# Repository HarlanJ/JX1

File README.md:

# JX1
The JX1 is an open source 3D printer in progress. It uses custom software on a Raspberry Pi and custom Arduino firmware. This project is created by John Harlan with help from Edward Green.

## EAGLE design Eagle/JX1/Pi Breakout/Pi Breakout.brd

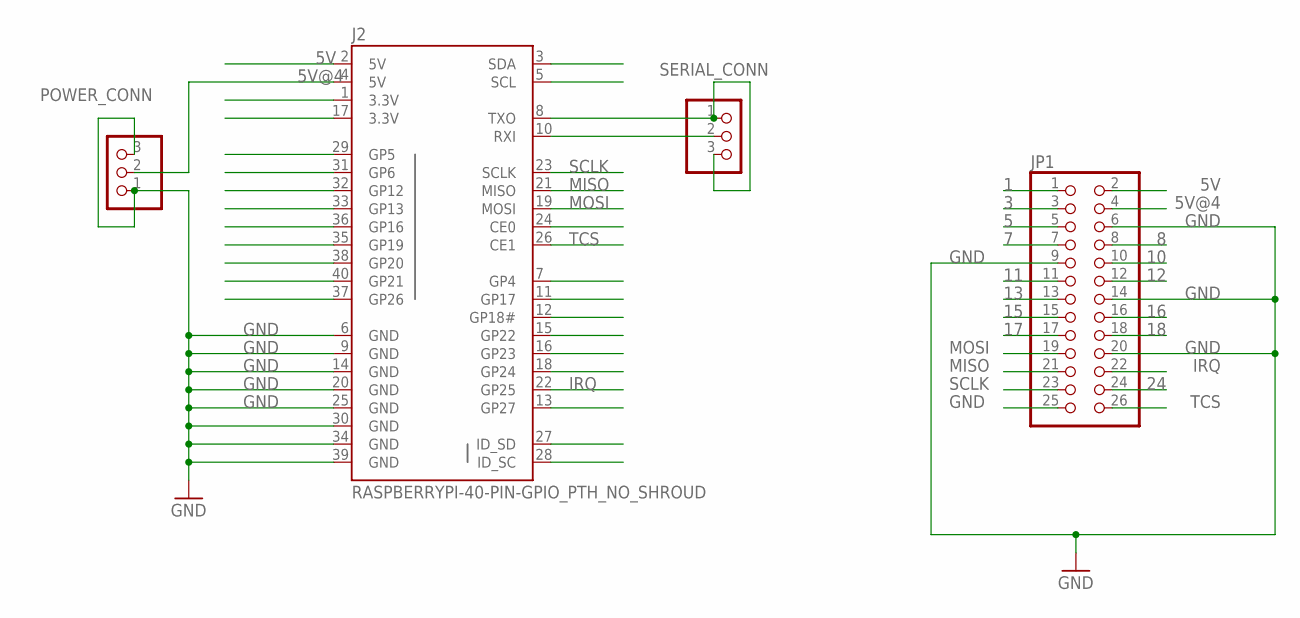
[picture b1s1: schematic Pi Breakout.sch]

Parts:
J2: RASPBERRYPI-40-PIN-GPIO_PTH_NO_SHROUD; 2X20
JP1: PINHD-2X13; 2X13
POWER_CONN: PINHD-1X3; 1X03
SERIAL_CONN: PINHD-1X3; 1X03

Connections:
1: JP1.1
3: JP1.3
5: JP1.5
5V: J2.2 (5V), JP1.2
5V@4: J2.4 (5V), JP1.4, POWER_CONN.2
7: JP1.7
8: JP1.8
10: JP1.10
11: JP1.11
12: JP1.12
13: JP1.13
15: JP1.15
16: JP1.16
17: JP1.17
18: JP1.18
24: JP1.24
GND: J2.6 (GND), J2.9 (GND), J2.14 (GND), J2.20 (GND), J2.25 (GND), J2.30 (GND), J2.34 (GND), J2.39 (GND), JP1.6, JP1.9, JP1.14, JP1.20, JP1.25, POWER_CONN.1, POWER_CONN.3
GP22: J2.15 (GP22)
IRQ: J2.22 (GP25), JP1.22
MISO: J2.21 (MISO), JP1.21
MOSI: J2.19 (MOSI), JP1.19
unnamed: J2.8 (TXO), SERIAL_CONN.1, SERIAL_CONN.3
unnamed: J2.10 (RXI), SERIAL_CONN.2
SCLK: J2.23 (SCLK), JP1.23
TCS: J2.26 (CE1), JP1.26

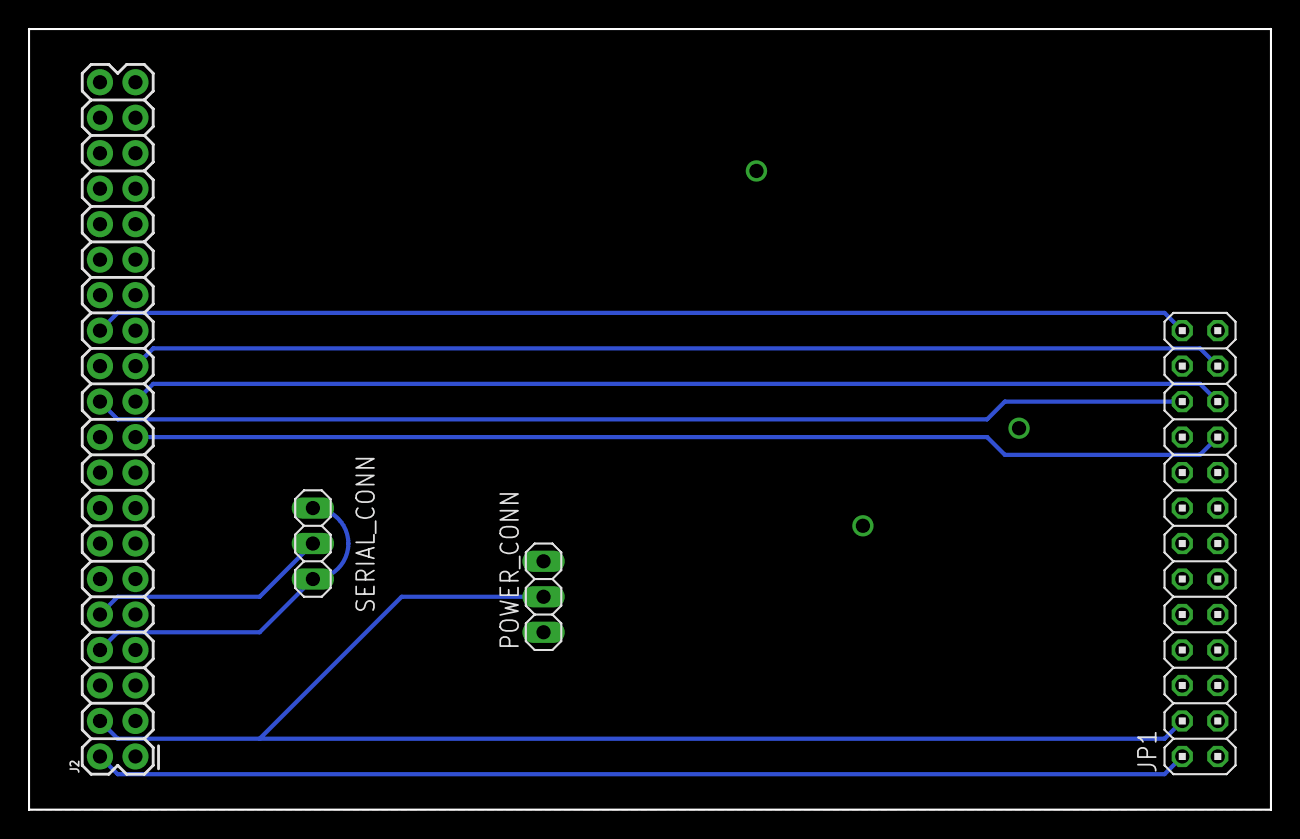
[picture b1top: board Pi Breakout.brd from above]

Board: 2 copper layers, 88.9 x 55.9 mm, 4 parts (0 on the bottom side), 10 nets.

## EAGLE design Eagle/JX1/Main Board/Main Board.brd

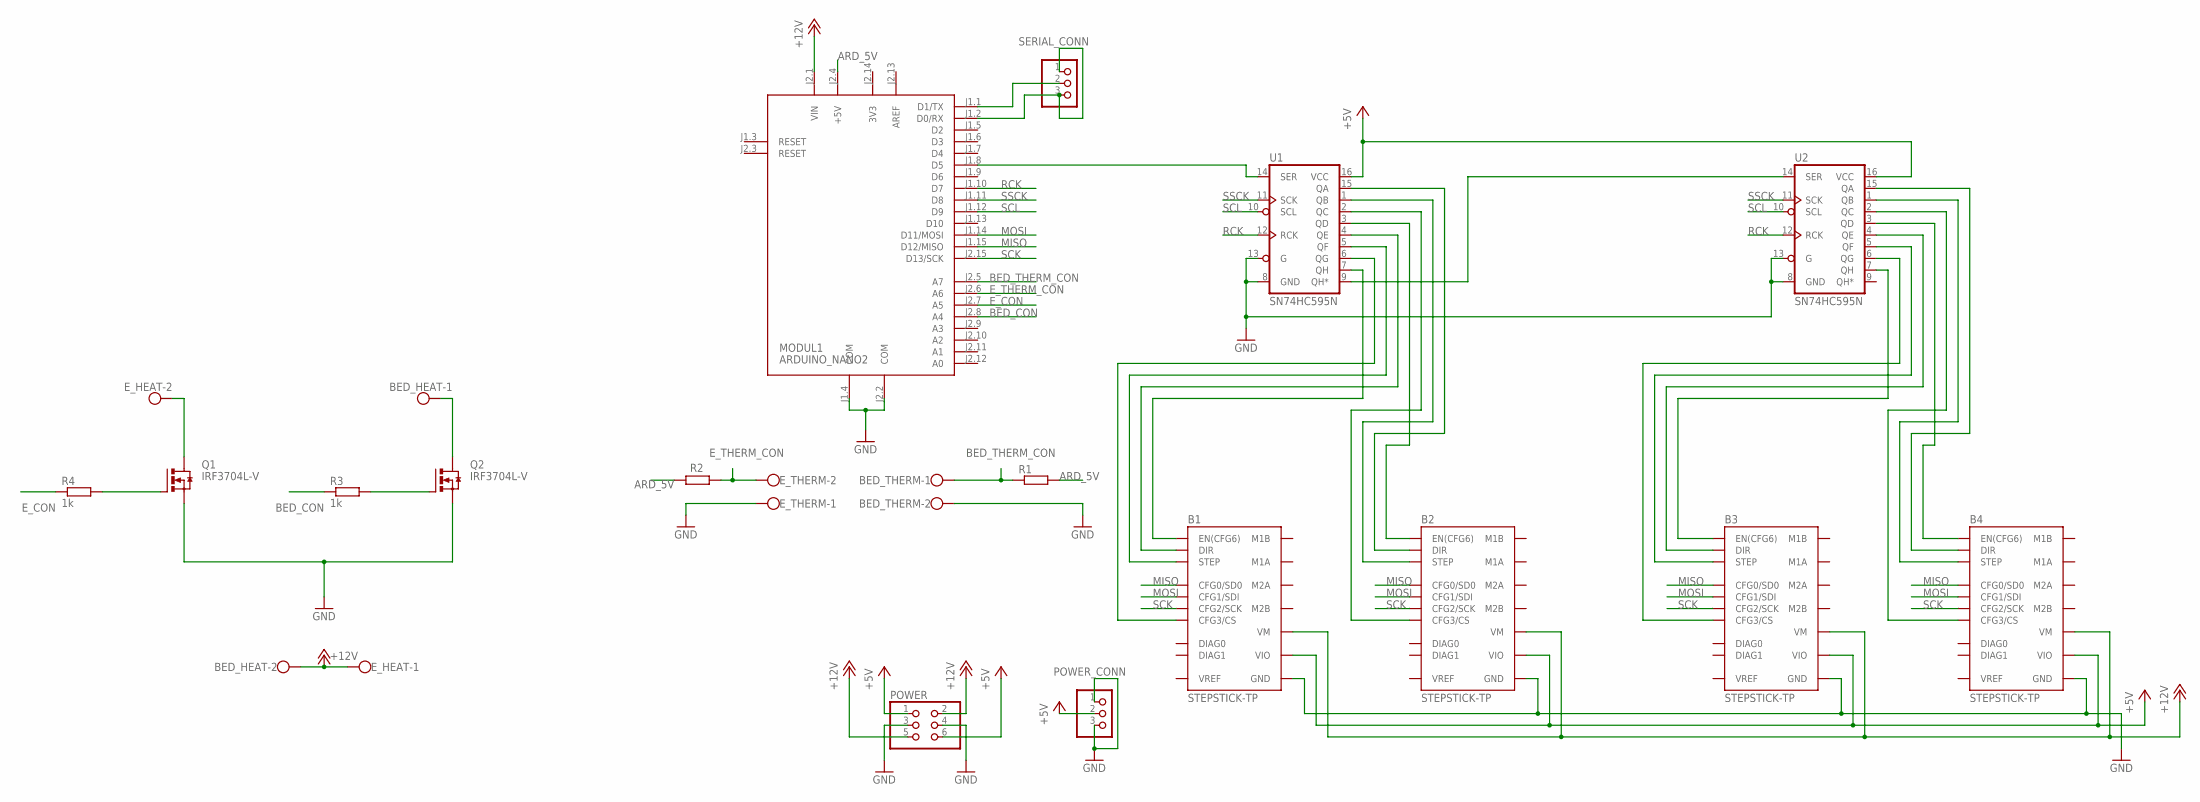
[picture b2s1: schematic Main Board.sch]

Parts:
B1, B2, B3, B4: STEPSTICK-TP; STEPSTICK_TP
BED_HEAT: W237-102
BED_THERM: W237-102
E_HEAT: W237-102
E_THERM: W237-102
MODUL1: ARDUINO_NANO2
POWER: PINHD-2X3; 2X03
POWER_CONN: PINHD-1X3; 1X03
Q1, Q2: IRF3704L-V; TO262-V
R1, R2: R0204/7; 0204/7
R3, R4: 1k; 0207/10
SERIAL_CONN: PINHD-1X3; 1X03
U1, U2: SN74HC595N; DIP16

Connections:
3V3: MODUL1.J2.14 (3V3)
+5V: B1.VIO, B2.VIO, B3.VIO, B4.VIO, POWER.1, POWER.6, POWER_CONN.2, U1.16 (VCC), U2.16 (VCC)
+12V: B1.VM, B2.VM, B3.VM, B4.VM, BED_HEAT.2, E_HEAT.1, MODUL1.J2.1 (VIN), POWER.2, POWER.5
ARD_5V: MODUL1.J2.4 (+5V), R1.2, R2.2
AREF: MODUL1.J2.13 (AREF)
BED_CON: MODUL1.J2.8 (A4), R3.1
BED_THERM_CON: BED_THERM.1, MODUL1.J2.5 (A7), R1.1
E_CON: MODUL1.J2.7 (A5), R4.1
E_THERM_CON: E_THERM.2, MODUL1.J2.6 (A6), R2.1
GND: B1.GND@1 (GND), B1.GND@2 (GND), B2.GND@1 (GND), B2.GND@2 (GND), B3.GND@1 (GND), B3.GND@2 (GND), B4.GND@1 (GND), B4.GND@2 (GND), BED_THERM.2, E_THERM.1, MODUL1.J1.4 (COM), MODUL1.J2.2 (COM), POWER.3, POWER.4, POWER_CONN.1, POWER_CONN.3, Q1.3 (S), Q2.3 (S), U1.8 (GND), U1.13 (G), U2.8 (GND), U2.13 (G)
MISO: B1.NC/CFG0 (CFG0/SD0), B2.NC/CFG0 (CFG0/SD0), B3.NC/CFG0 (CFG0/SD0), B4.NC/CFG0 (CFG0/SD0), MODUL1.J1.15 (D12/MISO)
MOSI: B1.CFG1 (CFG1/SDI), B2.CFG1 (CFG1/SDI), B3.CFG1 (CFG1/SDI), B4.CFG1 (CFG1/SDI), MODUL1.J1.14 (D11/MOSI)
unnamed: MODUL1.J1.1 (D1/TX), SERIAL_CONN.2
unnamed: U1.9 (QH*), U2.14 (SER)
unnamed: B2.CFG3 (CFG3/CS), U1.2 (QC)
unnamed: E_HEAT.2, Q1.2 (D)
unnamed: Q2.1 (G), R3.2
unnamed: BED_HEAT.1, Q2.2 (D)
unnamed: Q1.1 (G), R4.2
unnamed: B3.EN (EN(CFG6)), U2.7 (QH)
unnamed: B3.STEP, U2.5 (QF)
unnamed: B3.CFG3 (CFG3/CS), U2.6 (QG)
unnamed: B4.CFG3 (CFG3/CS), U2.2 (QC)
unnamed: B4.DIR, U2.15 (QA)
unnamed: B1.DIR, U1.4 (QE)
unnamed: B1.STEP, U1.5 (QF)
unnamed: MODUL1.J1.8 (D5), U1.14 (SER)
unnamed: B1.CFG3 (CFG3/CS), U1.6 (QG)
unnamed: B2.STEP, U1.1 (QB)
unnamed: B2.DIR, U1.15 (QA)
unnamed: B2.EN (EN(CFG6)), U1.3 (QD)
unnamed: MODUL1.J1.2 (D0/RX), SERIAL_CONN.1, SERIAL_CONN.3
unnamed: B1.EN (EN(CFG6)), U1.7 (QH)
unnamed: B3.DIR, U2.4 (QE)
unnamed: B4.EN (EN(CFG6)), U2.3 (QD)
unnamed: B4.STEP, U2.1 (QB)
RCK: MODUL1.J1.10 (D7), U1.12 (RCK), U2.12 (RCK)
SCK: B1.CFG2 (CFG2/SCK), B2.CFG2 (CFG2/SCK), B3.CFG2 (CFG2/SCK), B4.CFG2 (CFG2/SCK), MODUL1.J2.15 (D13/SCK)
SCL: MODUL1.J1.12 (D9), U1.10 (SCL), U2.10 (SCL)
SSCK: MODUL1.J1.11 (D8), U1.11 (SCK), U2.11 (SCK)

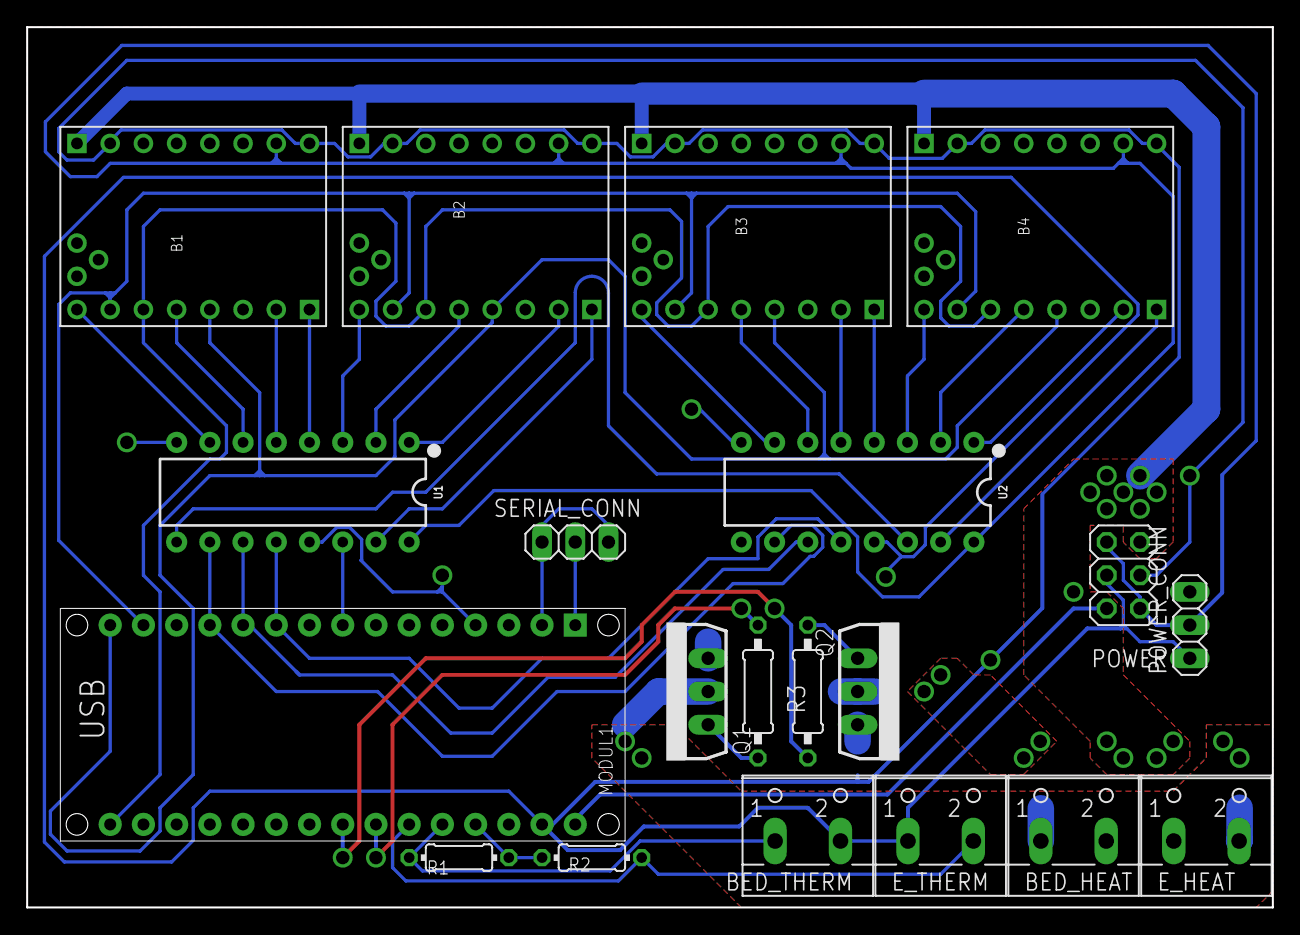
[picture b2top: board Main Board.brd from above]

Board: 2 copper layers, 95.2 x 67.3 mm, 20 parts (0 on the bottom side), 38 nets.

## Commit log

2018-08-29 Back upload (interface)
    Back versions of Interface software
2018-09-11 Added new interface version
    New version will be overwritten, using Github for version control, like a real developer!
2018-10-17 test
    testtest
2018-10-17 test removal
2018-10-17 Added compile
    Compiled for ARM.
2018-10-18 Added Arduino Sketch
    Added the beginning of a test for the TMC2130 interactions with Arduino.
2018-10-20 Edits to test sketch for silentStepSticks
2018-10-23 Added various TMC2130 tests
    Some small arduino sketches for various tests of my TMC2130s.
    Added the settings JSON file to the gitignore.
2018-10-23 Fixed the gitignore for the settings JSON
2018-10-24 Adjustments to the TMC tests
2018-10-31 Fiddling with Arduino Stuff and Started working on test for 4 drivers.
2018-11-01 Starting to communicate between nano and rpi
    Started trying to get the Serial communication between the arduino nano and the raspberry pi working
2019-01-08 Playing with Serial
2019-01-09 Numerous addjustments to Firmware and a LOT of nonsences with the interface.
2019-01-23 UGh
    Lots of toying with firmware to let serial and SPI happen
2019-01-24 Lots of fiddling around
2019-01-24 More fiddling
2019-01-24 Removed exported interface
2019-01-31 Removed '.jcode' from functioning code. It's not likely to be actually used at this time.
2019-01-31 Fixed a typing error with the Chopper configuration register for the drivers. Also changed the step timing while attempting to fix an unrelated problem.
2019-01-31 Added try-catch around Serial connection to allow easier debugging.
2019-01-31 Updated GitIgnore to ignore exports
2019-01-31 Fixed the previous gitignore fix!
2019-02-01 Some more fiddling
2019-02-07 Added garbage clearing to the Serial switch.
2019-02-07 Some organization of the Github. Moved old, single feature tests to a completely different folder: Old.
2019-02-07 Removed Some commented code.
2019-04-08 Began work on actual firmware, moving from tests.
2019-04-08 Added schematics and board files
2019-04-09 More board Changes
2019-04-10 Schematic and board changes
2019-04-10 Hand-routing the board
    Made changes to pin connections for better, neater routing.
2019-04-10 Routed Main Board
2019-04-11 Started moving traces to make room for thermal stuff
2019-04-11 Added and connected thermistor terminals
    Also added terminals for bed and extruder, but did not connect them.
2019-04-11 Beefed up 12V in traces
2019-04-12 Worked on heater traces some more.
2019-04-12 Started added power mosfets for heaters
2019-04-12 Finished thermal connections
2019-04-13 *Actually* finished thermal connections
2019-04-14 Began integrating shift registers and driver control code.
2019-04-15 Began implementing driver control.
2019-04-16 Finished up the pi breakout
2019-04-18 Added comments to the Arduino firmware
2019-04-18 Fixes to breakout
2019-06-09 Re-organized repo a bit
2019-07-28 Actually enabled Serial on the nano.
    No wonder it wasn't working...
2019-07-28 Added Some Serial Debug
2019-07-28 Export for RPI
2019-09-03 Added list of gcodes and what they do

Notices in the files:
parts and their libraries:
SparkFun-IC-Logic: Licensing: Creative Commons ShareAlike 4.0 International - https://creativecommons.org/licenses/by-sa/4.0
